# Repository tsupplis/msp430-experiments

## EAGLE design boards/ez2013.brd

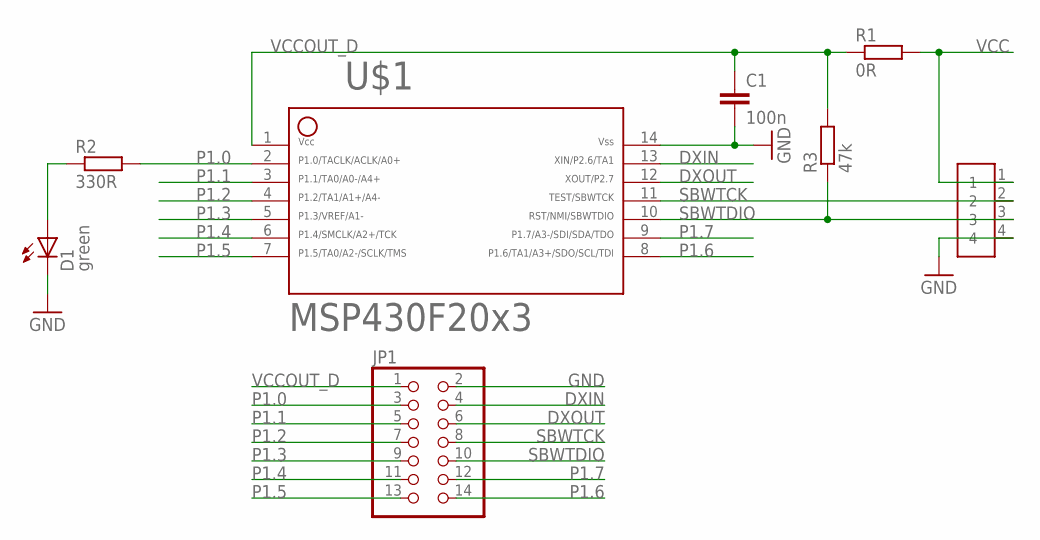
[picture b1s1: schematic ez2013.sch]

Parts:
C1: 100n; C0805
D1: green; CHIPLED_1206
JP1: PINHD-2X7; 2X07
R1: 0R; R0805
R2: 330R; R0805
R3: 47k; R0805
U$1: F20X3---PW14; PW14
U$2: PINHD-1X4-1.27; 1X04-1.27

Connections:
DXIN: JP1.4, U$1.13
DXOUT: JP1.6, U$1.12
GND: C1.2, D1.C, JP1.2, U$1.14, U$2.4
unnamed: D1.A, R2.1
P1.0: JP1.3, R2.2, U$1.2
P1.1: JP1.5, U$1.3
P1.2: JP1.7, U$1.4
P1.3: JP1.9, U$1.5
P1.4: JP1.11, U$1.6
P1.5: JP1.13, U$1.7
P1.6: JP1.14, U$1.8
P1.7: JP1.12, U$1.9
SBWTCK: JP1.8, U$1.11, U$2.2
SBWTDIO: JP1.10, R3.1, U$1.10, U$2.3
VCC: R1.2, U$2.1
VCCOUT_D: C1.1, JP1.1, R1.1, R3.2, U$1.1

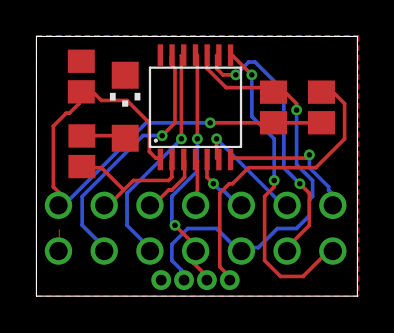
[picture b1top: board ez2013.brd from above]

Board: 2 copper layers, 17.8 x 14.4 mm, 8 parts (1 on the bottom side), 16 nets.

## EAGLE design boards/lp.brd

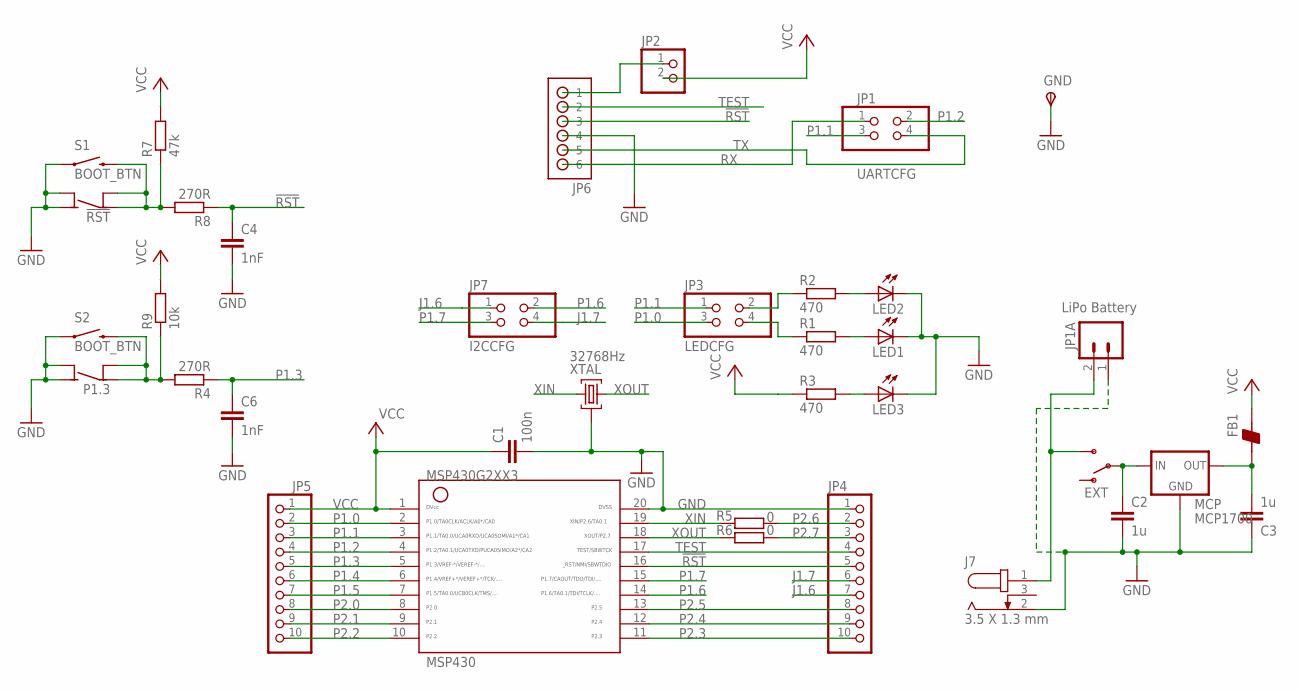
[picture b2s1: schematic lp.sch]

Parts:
!RST: !RST; 6MMTACTILE_4PIN
C1: 100n; C0805
C2, C3: 1u; C0805
C4, C6: 1nF; C0805
FB1: BEAD-0805; 0805
GND: TPSTP20R; TP20R
J7: 3.5 X 1.3 mm; 3.5X1.3MM_DC_JACK
JP1: UARTCFG; 2X02
JP1A: LiPo Battery; JST-2-PTH
JP2: PINHD-1X2; 1X02
JP3: LEDCFG; 2X02
JP4, JP5: PH1X10OCT076; PH1X10OCT76
JP6: No Load; HDR-1X6_OFFSET
JP7: I2CCFG; 2X02
LED1, LED2, LED3: 0; CHIPLED_1206
MCP: MCP1700; SOT-23
MSP430: MSP430N; DIP20_HEX
ON: EXT; SWITCH-SPDT
P1.3: P1.3; 6MMTACTILE_4PIN
R1, R2, R3: 470; R0805
R4, R8: 270R; R0805
R5, R6: 0; R0805
R7: 47k; R0805
R9: 10k; R0805
S1, S2: BOOT_BTN; TACTILE-SWITCH-1101NE
XTAL: 32768Hz; QUARZ5

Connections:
!RST: C4.1, JP4.5, JP6.3, MSP430.16, R8.1
GND: !RST.A1 (NO), !RST.A2 (NO), C1.2, C2.2, C3.1, C4.2, C6.2, GND.TP, J7.2, JP1A.1, JP4.1, JP6.4, LED1.C, LED2.C, LED3.C, MCP.1 (GND), MSP430.20, P1.3.A1 (NO), P1.3.A2 (NO), S1.1, S2.1, XTAL.GND@0 (0)
J1.6: JP4.7, JP7.1
J1.7: JP4.6, JP7.4
unnamed: JP3.2, R2.1
unnamed: JP3.4, R1.1
unnamed: C2.1, MCP.3 (IN), ON.2
unnamed: P1.3.B1 (COM), P1.3.B2 (COM), R4.2, R9.1, S2.2
unnamed: !RST.B1 (COM), !RST.B2 (COM), R7.1, R8.2, S1.2
unnamed: C3.2, FB1.1, MCP.2 (OUT)
unnamed: LED3.A, R3.2
unnamed: LED1.A, R1.2
unnamed: LED2.A, R2.2
P1.0: JP3.3, JP5.2, MSP430.2
P1.1: JP1.3, JP3.1, JP5.3, MSP430.3
P1.2: JP1.2, JP5.4, MSP430.4
P1.3: C6.1, JP5.5, MSP430.5, R4.1
P1.4: JP5.6, MSP430.6
P1.5: JP5.7, MSP430.7
P1.6: JP7.2, MSP430.14
P1.7: JP7.3, MSP430.15
P2.0: JP5.8, MSP430.8
P2.1: JP5.9, MSP430.9
P2.2: JP5.10, MSP430.10
P2.3: JP4.10, MSP430.11
P2.4: JP4.9, MSP430.12
P2.5: JP4.8, MSP430.13
P2.6: JP4.2, R5.2
P2.7: JP4.3, R6.2
RX: JP1.1, JP6.6
TEST: JP4.4, JP6.2, MSP430.17
TX: JP1.4, JP6.5
VCC: C1.1, FB1.2, JP2.2, JP5.1, MSP430.1, R3.1, R7.2, R9.2
VCCEXT: J7.1, JP1A.2, ON.3 (S)
VCCFET: JP2.1, JP6.1
XIN: MSP430.19, R5.1, XTAL.2
XOUT: MSP430.18, R6.1, XTAL.1

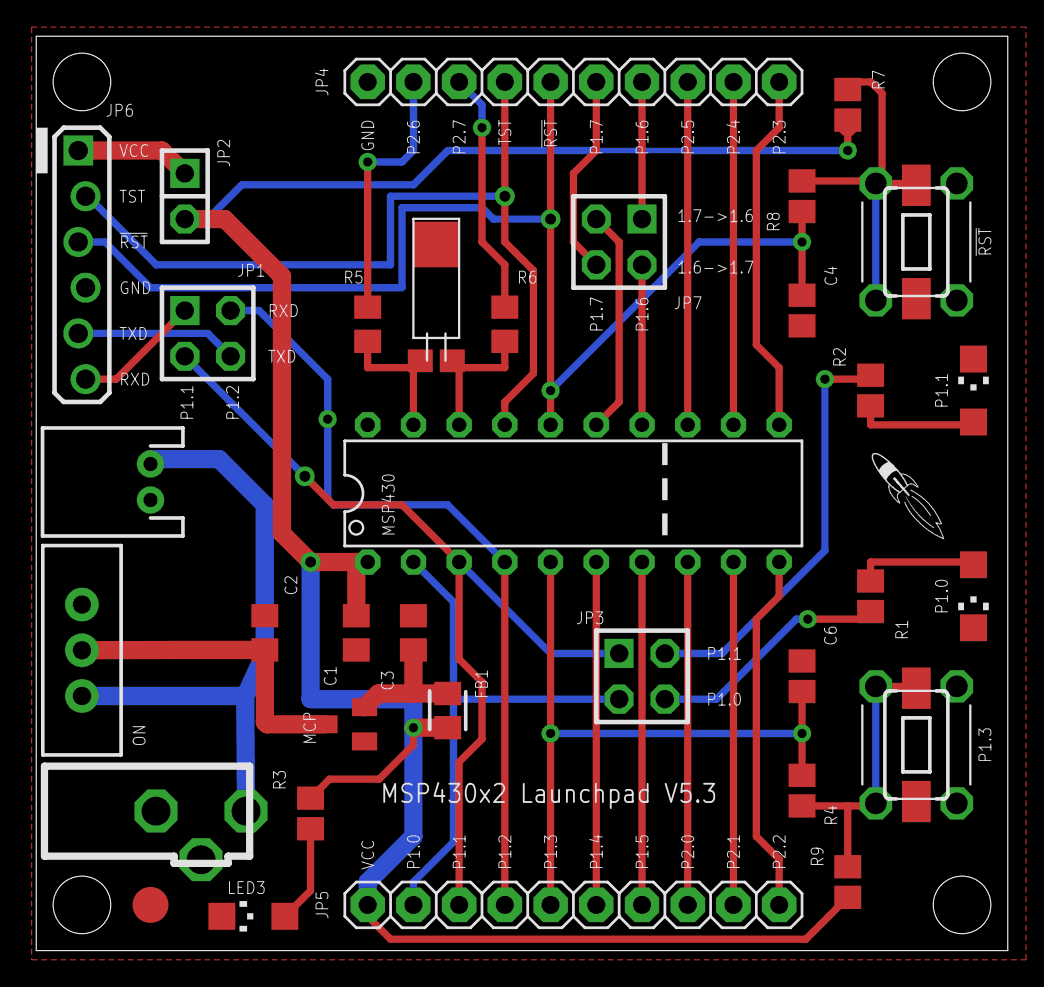
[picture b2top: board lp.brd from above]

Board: 2 copper layers, 54.0 x 50.8 mm, 37 parts (0 on the bottom side), 37 nets.

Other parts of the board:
U$2: LOGO-ROCKET

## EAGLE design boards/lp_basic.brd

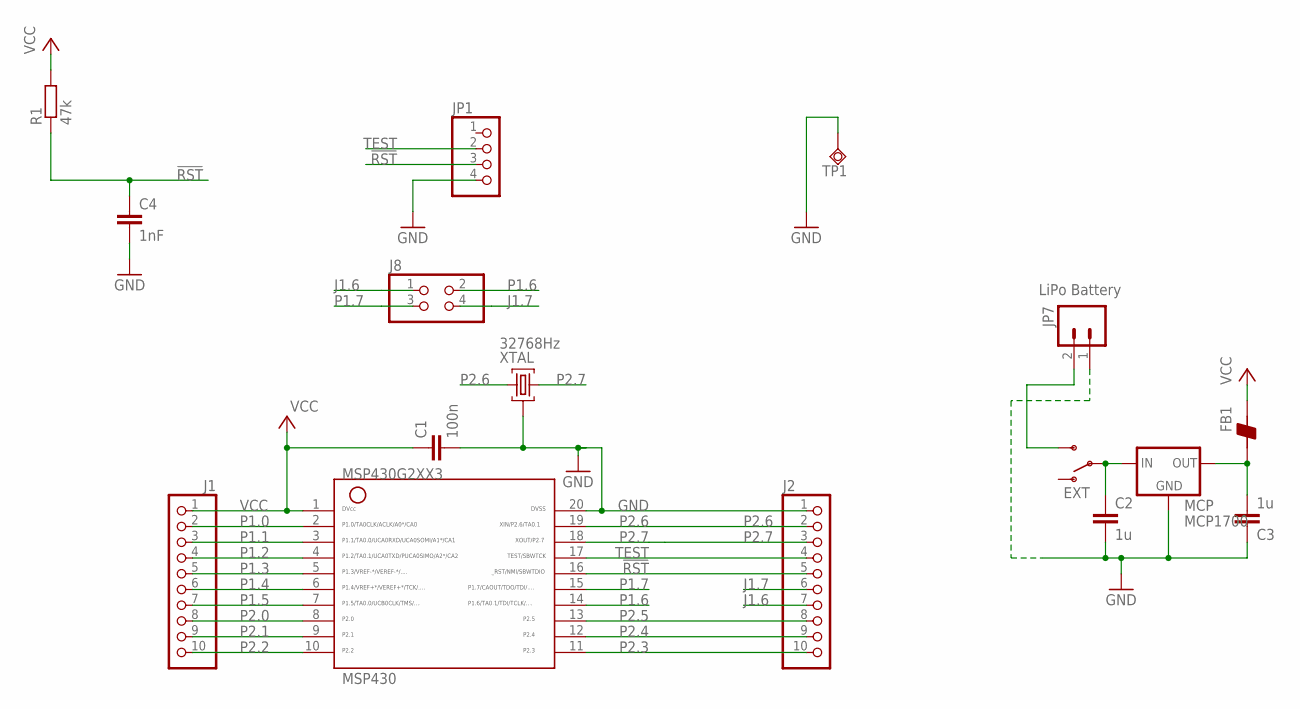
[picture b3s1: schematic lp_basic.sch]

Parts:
C1: 100n; C0805
C2, C3: 1u; C0805
C4: 1nF; C0805
FB1: BEAD-0805; 0805
J1, J2: PH1X10OCT076; PH1X10OCT76
J8: PINHD-2X2; 2X02
JP1: PINHD-1X4; 1X04
JP7: LiPo Battery; JST-2-PTH
MCP: MCP1700; SOT-23
MSP430: MSP430N; DIP20_HEX
ON: EXT; SWITCH-SPDT
R1: 47k; R0805
TP1: TPSQTP20R; TP20R
XTAL: 32768Hz; QUARZ5

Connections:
!RST: C4.1, J2.5, JP1.3, MSP430.16, R1.1
GND: C1.2, C2.2, C3.1, C4.2, J2.1, JP1.4, JP7.1, MCP.1 (GND), MSP430.20, TP1.TP, XTAL.GND@0 (0)
J1.6: J2.7, J8.1
J1.7: J2.6, J8.4
unnamed: C2.1, MCP.3 (IN), ON.2
unnamed: C3.2, FB1.1, MCP.2 (OUT)
P1.0: J1.2, MSP430.2
P1.1: J1.3, MSP430.3
P1.2: J1.4, MSP430.4
P1.3: J1.5, MSP430.5
P1.4: J1.6, MSP430.6
P1.5: J1.7, MSP430.7
P1.6: J8.2, MSP430.14
P1.7: J8.3, MSP430.15
P2.0: J1.8, MSP430.8
P2.1: J1.9, MSP430.9
P2.2: J1.10, MSP430.10
P2.3: J2.10, MSP430.11
P2.4: J2.9, MSP430.12
P2.5: J2.8, MSP430.13
P2.6: J2.2, MSP430.19, XTAL.2
P2.7: J2.3, MSP430.18, XTAL.1
TEST: J2.4, JP1.2, MSP430.17
VCC: C1.1, FB1.2, J1.1, MSP430.1, R1.2
VCCEXT: JP7.2, ON.3 (S)

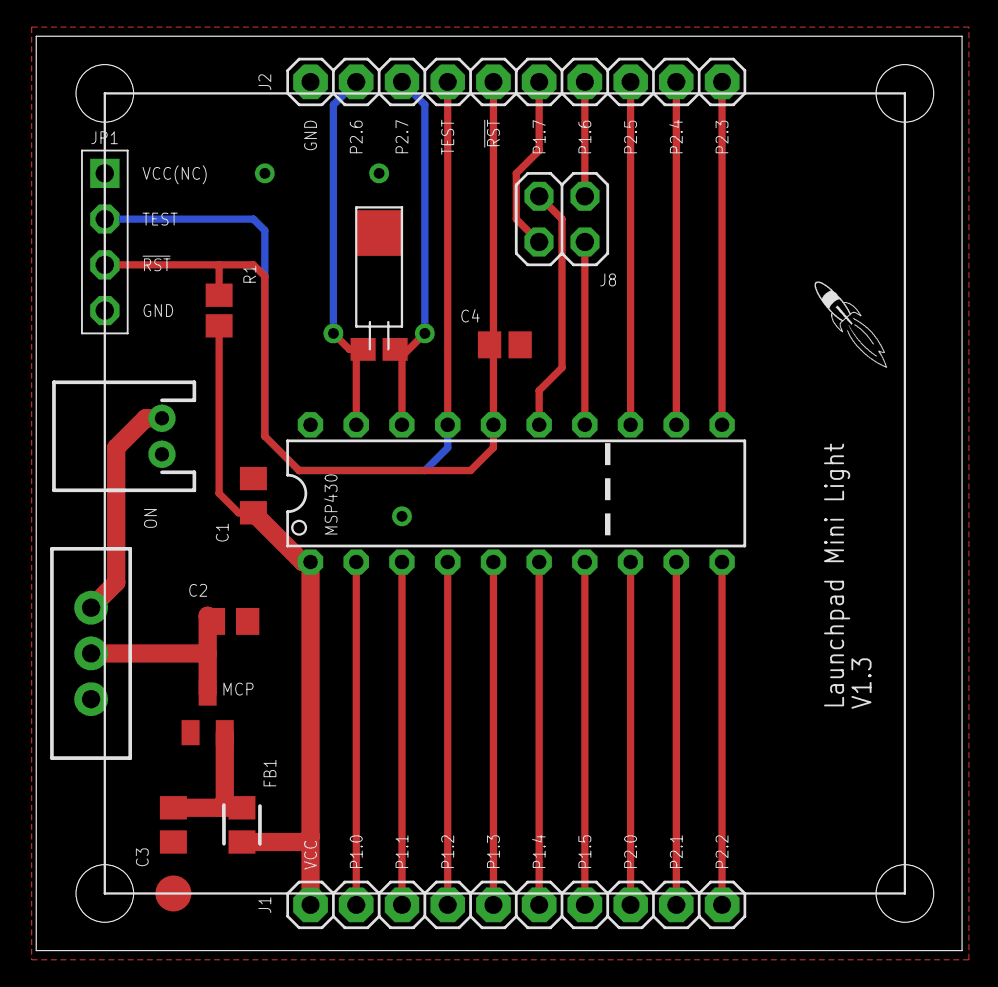
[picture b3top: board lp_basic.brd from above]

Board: 2 copper layers, 51.4 x 50.8 mm, 18 parts (0 on the bottom side), 25 nets.

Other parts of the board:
U$1: LP_CANVAS
U$2: LOGO-ROCKET

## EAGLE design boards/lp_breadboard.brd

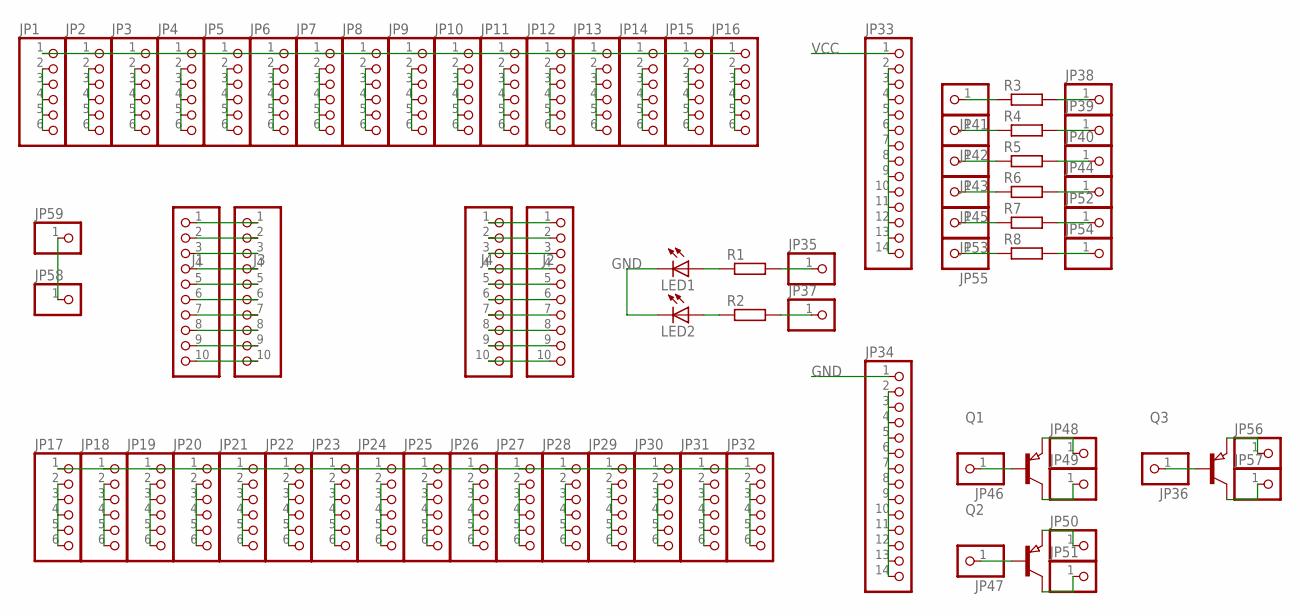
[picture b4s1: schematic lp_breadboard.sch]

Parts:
J1, J2, J3, J4: PINHD-1X10; 1X10
JP1, JP2, JP3, JP4, JP5, JP6, JP7, JP8, JP9, JP10, JP11, JP12, JP13, JP14, JP15, JP16, JP17, JP18, JP19, JP20, JP21, JP22, JP23, JP24, JP25, JP26, JP27, JP28, JP29, JP30, JP31, JP32: PINHD-1X6; 1X06
JP33, JP34: PINHD-1X14; 1X14
JP35, JP36, JP37, JP38, JP39, JP40, JP41, JP42, JP43, JP44, JP45, JP46, JP47, JP48, JP49, JP50, JP51, JP52, JP53, JP54, JP55, JP56, JP57, JP58, JP59: PINHD-1X1; 1X01
LED1, LED2: LEDCHIPLED_1206; CHIPLED_1206
Q1, Q2, Q3: PNP-TRANSISTOR_SOT23; SOT23
R1, R2, R3, R4, R5, R6, R7, R8: R-EU_R0805; R0805

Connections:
GND: J2.1, J4.1, JP1.1, JP2.1, JP3.1, JP4.1, JP5.1, JP6.1, JP7.1, JP8.1, JP9.1, JP10.1, JP11.1, JP12.1, JP13.1, JP14.1, JP15.1, JP16.1, JP34.1, JP58.1, JP59.1, LED1.C, LED2.C
unnamed: JP1.2, JP1.3, JP1.4, JP1.5, JP1.6
unnamed: J1.2, J3.2
unnamed: JP6.2, JP6.3, JP6.4, JP6.5, JP6.6
unnamed: JP2.2, JP2.3, JP2.4, JP2.5, JP2.6
unnamed: JP24.2, JP24.3, JP24.4, JP24.5, JP24.6
unnamed: JP3.2, JP3.3, JP3.4, JP3.5, JP3.6
unnamed: JP4.2, JP4.3, JP4.4, JP4.5, JP4.6
unnamed: JP17.2, JP17.3, JP17.4, JP17.5, JP17.6
unnamed: JP18.2, JP18.3, JP18.4, JP18.5, JP18.6
unnamed: JP19.2, JP19.3, JP19.4, JP19.5, JP19.6
unnamed: JP20.2, JP20.3, JP20.4, JP20.5, JP20.6
unnamed: JP7.2, JP7.3, JP7.4, JP7.5, JP7.6
unnamed: JP22.2, JP22.3, JP22.4, JP22.5, JP22.6
unnamed: JP21.2, JP21.3, JP21.4, JP21.5, JP21.6
unnamed: J2.2, J4.2
unnamed: J2.10, J4.10
unnamed: JP8.2, JP8.3, JP8.4, JP8.5, JP8.6
unnamed: JP9.2, JP9.3, JP9.4, JP9.5, JP9.6
unnamed: JP10.2, JP10.3, JP10.4, JP10.5, JP10.6
unnamed: JP32.2, JP32.3, JP32.4, JP32.5, JP32.6
unnamed: J1.10, J3.10
unnamed: JP11.2, JP11.3, JP11.4, JP11.5, JP11.6
unnamed: JP31.2, JP31.3, JP31.4, JP31.5, JP31.6
unnamed: JP23.2, JP23.3, JP23.4, JP23.5, JP23.6
unnamed: J2.3, J4.3
unnamed: J2.4, J4.4
unnamed: J1.3, J3.3
unnamed: JP12.2, JP12.3, JP12.4, JP12.5, JP12.6
unnamed: JP13.2, JP13.3, JP13.4, JP13.5, JP13.6
unnamed: J1.4, J3.4
unnamed: J1.5, J3.5
unnamed: JP14.2, JP14.3, JP14.4, JP14.5, JP14.6
unnamed: JP15.2, JP15.3, JP15.4, JP15.5, JP15.6
unnamed: JP16.2, JP16.3, JP16.4, JP16.5, JP16.6
unnamed: J1.6, J3.6
unnamed: J2.5, J4.5
unnamed: J2.6, J4.6
unnamed: JP30.2, JP30.3, JP30.4, JP30.5, JP30.6
unnamed: JP5.2, JP5.3, JP5.4, JP5.5, JP5.6
unnamed: J1.7, J3.7
unnamed: J2.7, J4.7
unnamed: JP25.2, JP25.3, JP25.4, JP25.5, JP25.6
unnamed: J1.8, J3.8
unnamed: J1.9, J3.9
unnamed: J2.8, J4.8
unnamed: JP26.2, JP26.3, JP26.4, JP26.5, JP26.6
unnamed: J2.9, J4.9
unnamed: JP27.2, JP27.3, JP27.4, JP27.5, JP27.6
unnamed: JP28.2, JP28.3, JP28.4, JP28.5, JP28.6
unnamed: JP29.2, JP29.3, JP29.4, JP29.5, JP29.6
unnamed: JP33.2, JP33.3, JP33.4, JP33.5, JP33.6, JP33.7, JP33.8, JP33.9, JP33.10, JP33.11, JP33.12, JP33.13, JP33.14
unnamed: JP36.1, Q3.1 (B)
unnamed: JP34.2, JP34.3, JP34.4, JP34.5, JP34.6, JP34.7, JP34.8, JP34.9, JP34.10, JP34.11, JP34.12, JP34.13, JP34.14
unnamed: LED1.A, R1.1
unnamed: JP56.1, Q3.2 (E)
unnamed: JP57.1, Q3.3 (C)
unnamed: JP35.1, R1.2
unnamed: LED2.A, R2.1
unnamed: JP37.1, R2.2
unnamed: JP41.1, R3.1
unnamed: JP42.1, R4.1
unnamed: JP43.1, R5.1
unnamed: JP38.1, R3.2
unnamed: JP39.1, R4.2
unnamed: JP40.1, R5.2
unnamed: JP45.1, R6.1
unnamed: JP44.1, R6.2
unnamed: JP46.1, Q1.1 (B)
unnamed: JP47.1, Q2.1 (B)
unnamed: JP48.1, Q1.2 (E)
unnamed: JP49.1, Q1.3 (C)
unnamed: JP50.1, Q2.2 (E)
unnamed: JP51.1, Q2.3 (C)
unnamed: JP53.1, R7.1
unnamed: JP52.1, R7.2
unnamed: JP55.1, R8.1
unnamed: JP54.1, R8.2
VCC: J1.1, J3.1, JP17.1, JP18.1, JP19.1, JP20.1, JP21.1, JP22.1, JP23.1, JP24.1, JP25.1, JP26.1, JP27.1, JP28.1, JP29.1, JP30.1, JP31.1, JP32.1, JP33.1

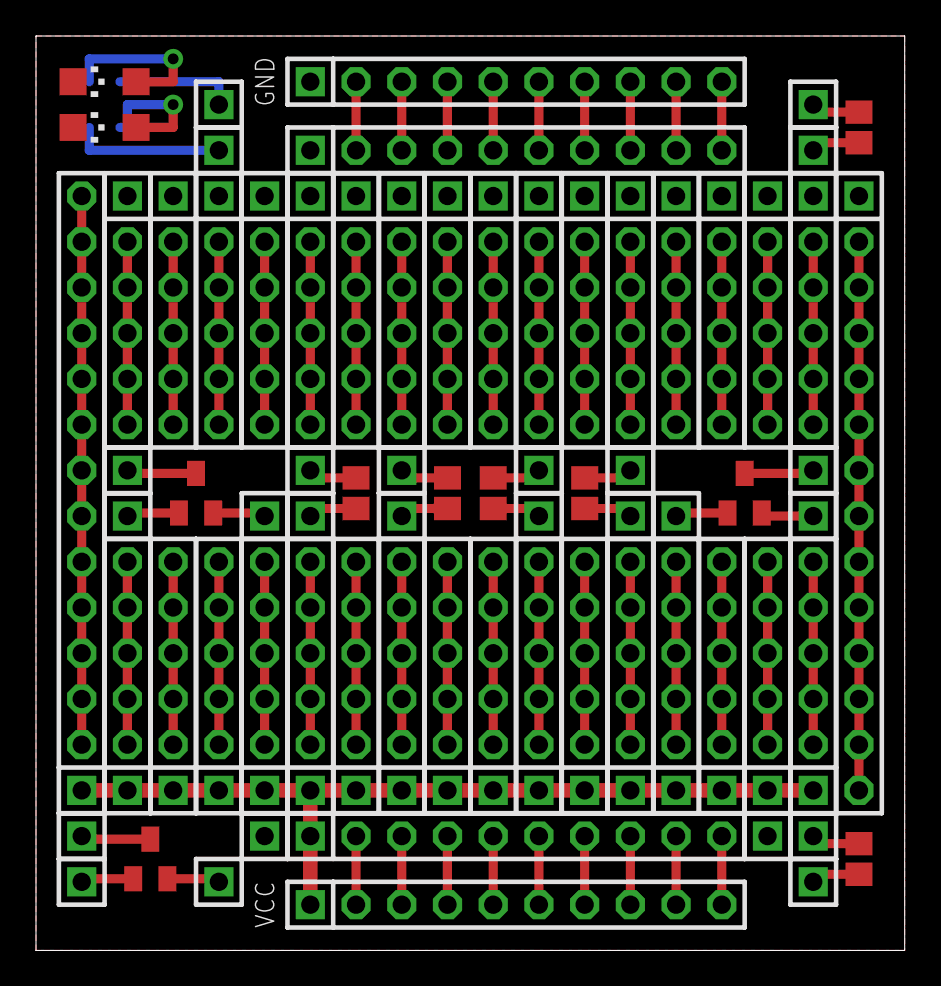
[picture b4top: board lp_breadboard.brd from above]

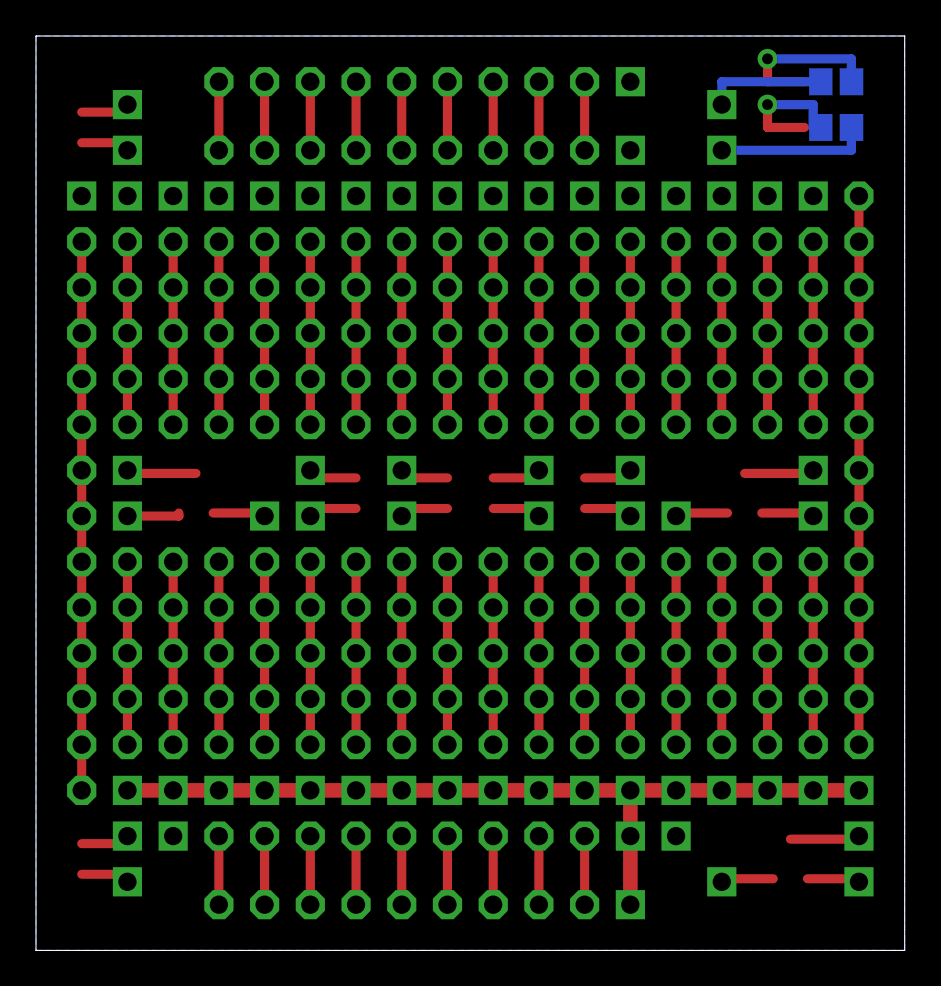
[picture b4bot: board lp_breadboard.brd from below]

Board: 2 copper layers, 48.3 x 50.8 mm, 76 parts (2 on the bottom side), 79 nets.

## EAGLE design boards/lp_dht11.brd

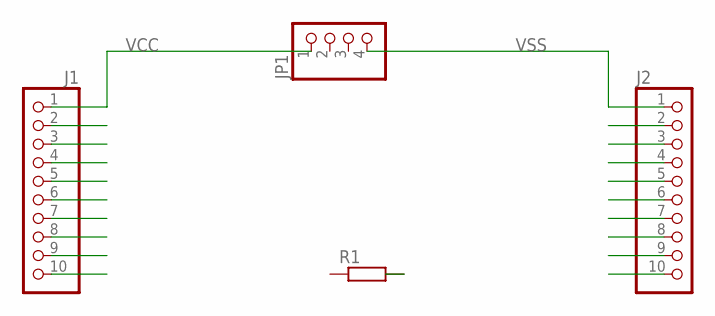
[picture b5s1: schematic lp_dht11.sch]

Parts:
J1, J2: PH1X10OCT076; PH1X10OCT76
JP1: PINHD-1X4; 1X04
R1: R-EU_0207/10; 0207/10

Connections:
VCC: J1.1, JP1.1
VSS: J2.1, JP1.4

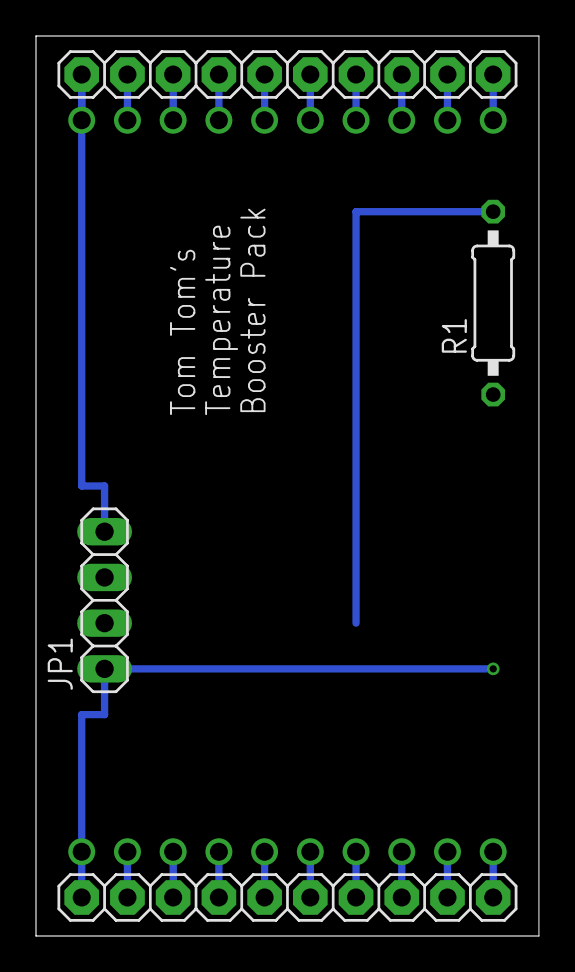
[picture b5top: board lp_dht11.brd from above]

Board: 2 copper layers, 27.9 x 50.0 mm, 4 parts (0 on the bottom side), 2 nets.

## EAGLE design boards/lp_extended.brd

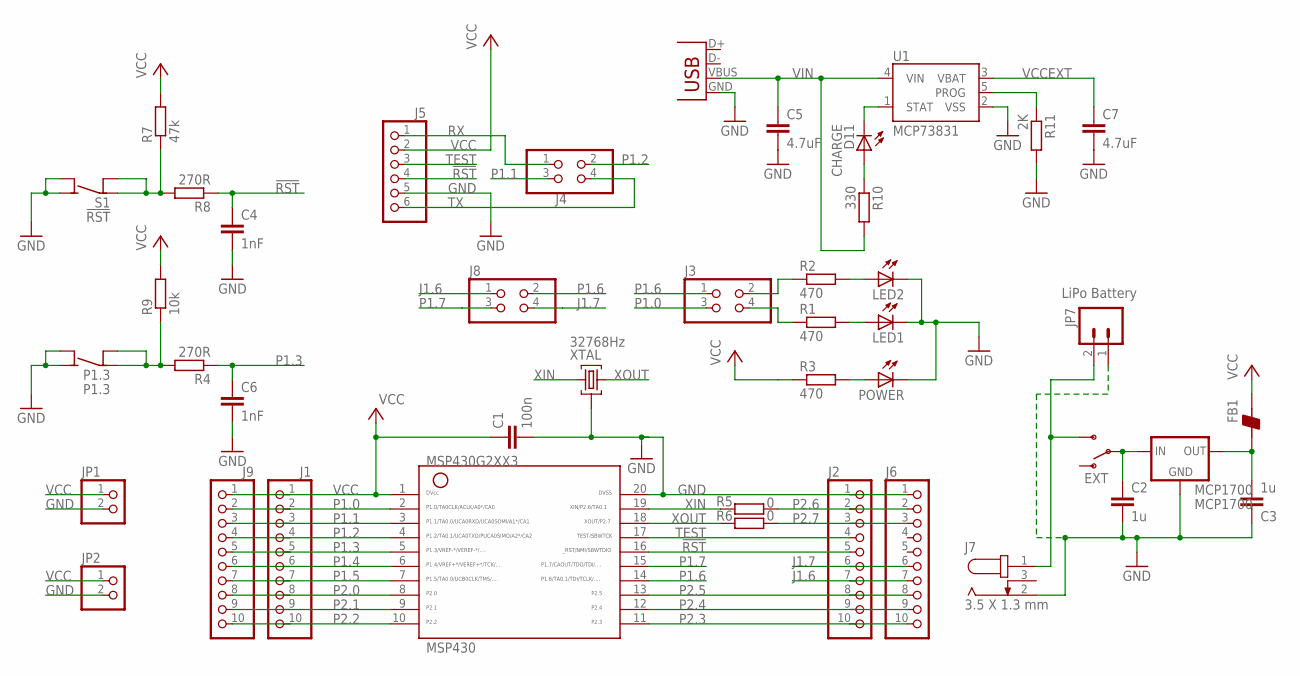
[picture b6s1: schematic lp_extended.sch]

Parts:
C1: 100n; C0805
C2, C3: 1u; C0805
C4, C6: 1nF; C0805
C5, C7: 4.7uF; C0805
D11: CHARGE; CHIPLED_1206
FB1: BEAD-0805; 0805
J1, J2, J6, J9: PH1X10OCT076; PH1X10OCT76
J3, J4, J8: PINHD-2X2; 2X02
J5: PINHD-1X6; 1X06
J7: 3.5 X 1.3 mm; 3.5X1.3MM_DC_JACK
JP1, JP2: PINHD-1X2; 1X02
JP7: LiPo Battery; JST-2-PTH
LED1, LED2: LEDCHIPLED_1206; CHIPLED_1206
MCP1700: MCP1700; SOT-23
MSP430: MSP430N; DIP20_HEX
ON: EXT; SWITCH-SPDT
P1.3: P1.3; 6MMTACTILE_4PIN
POWER: LEDCHIPLED_1206; CHIPLED_1206
R1, R2, R3: 470; R0805
R4, R8: 270R; R0805
R5, R6: 0; R0805
R7: 47k; R0805
R9: 10k; R0805
R10: 330; R0805
R11: 2K; R0805
S1: !RST; 6MMTACTILE_4PIN
U1: MCP73831; SOT23-5
X1: Mini USB; USB-MINIB-OLD
XTAL: 32768Hz; QUARZ5

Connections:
!RST: C4.1, J2.5, J5.4, MSP430.16, R8.1
GND: C1.2, C2.2, C3.1, C4.2, C5.2, C6.2, C7.2, J2.1, J5.5, J6.1, J7.2, JP1.2, JP2.2, JP7.1, LED1.C, LED2.C, MCP1700.1 (GND), MSP430.20, P1.3.A1 (NO), P1.3.A2 (NO), POWER.C, R11.2, S1.A1 (NO), S1.A2 (NO), U1.2 (VSS), X1.GND, XTAL.GND@0 (0)
J1.6: J2.7, J6.7, J8.1
J1.7: J2.6, J6.6, J8.4
unnamed: J3.2, R2.1
unnamed: J3.4, R1.1
unnamed: C2.1, MCP1700.3 (IN), ON.2
unnamed: P1.3.B1 (COM), P1.3.B2 (COM), R4.2, R9.1
unnamed: R7.1, R8.2, S1.B1 (COM), S1.B2 (COM)
unnamed: C3.2, FB1.1, MCP1700.2 (OUT)
unnamed: D11.A, R10.1
unnamed: POWER.A, R3.2
unnamed: LED1.A, R1.2
unnamed: LED2.A, R2.2
P1.0: J1.2, J3.3, J9.2, MSP430.2
P1.1: J1.3, J4.3, J9.3, MSP430.3
P1.2: J1.4, J4.2, J9.4, MSP430.4
P1.3: C6.1, J1.5, J9.5, MSP430.5, R4.1
P1.4: J1.6, J9.6, MSP430.6
P1.5: J1.7, J9.7, MSP430.7
P1.6: J3.1, J8.2, MSP430.14
P1.7: J8.3, MSP430.15
P2.0: J1.8, J9.8, MSP430.8
P2.1: J1.9, J9.9, MSP430.9
P2.2: J1.10, J9.10, MSP430.10
P2.3: J2.10, J6.10, MSP430.11
P2.4: J2.9, J6.9, MSP430.12
P2.5: J2.8, J6.8, MSP430.13
P2.6: J2.2, J6.2, R5.2
P2.7: J2.3, J6.3, R6.2
PROG: R11.1, U1.5 (PROG)
RX: J4.1, J5.1
STAT: D11.C, U1.1 (STAT)
TEST: J2.4, J5.3, MSP430.17
TX: J4.4, J5.6
VCC: C1.1, FB1.2, J1.1, J5.2, J9.1, JP1.1, JP2.1, MSP430.1, R3.1, R7.2, R9.2
VCCEXT: C7.1, J7.1, JP7.2, ON.3 (S), U1.3 (VBAT)
VIN: C5.1, R10.2, U1.4 (VIN), X1.VBUS
XIN: MSP430.19, R5.1, XTAL.2
XOUT: MSP430.18, R6.1, XTAL.1

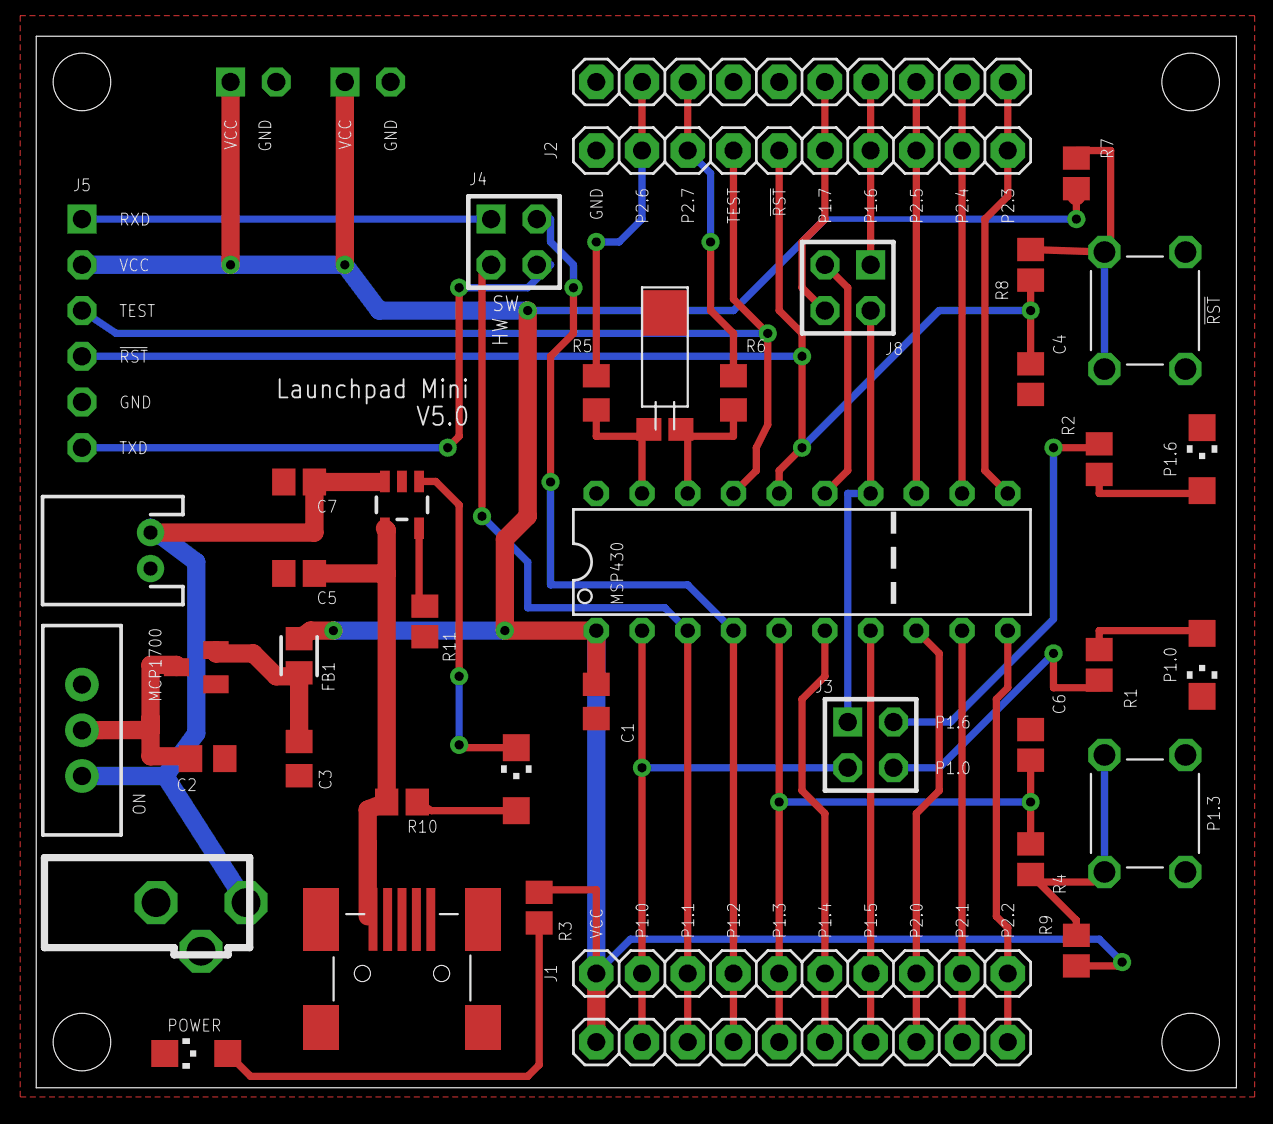
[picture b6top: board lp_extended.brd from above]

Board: 2 copper layers, 66.7 x 58.4 mm, 43 parts (0 on the bottom side), 40 nets.

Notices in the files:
parts and their libraries:
SparkFun: Licensing: CC v3.0 Share-Alike You are welcome to use this library for commercial purposes.
SparkFun-Electromechanical: Licensing: Creative Commons ShareAlike 4.0 International - https://creativecommons.org/licenses/by-sa/4.0
